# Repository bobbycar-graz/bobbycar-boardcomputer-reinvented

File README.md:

# bobbycar-boardcomputer-reinvented
This is a project to reinvent the current board-computer. It is still based on ESP32, but has some new features in hardware and a completely rewritten software.

## Changes

- Updated PCB
  - 2nd Microcontroller for reading the potentiometers
  - Split entertainment / display / cloud from important things
  - Add on-board USB C flasher for both MCUs
  - Newer ESP32 module (ESP32-S3)
- Rewritten software
  - Written from scratch
  - Updated Librarys
  - Programmed for easier customization
  - Toolchains for generating icons etc.

## Documentation
- [PCB](kicad/README.md)
- [Entertainment Firmware](entertainment-firmware/README.md)
- [Input Firmware](input-firmware/README.md)

## New Structure

The idea is to split the old board-computer into multiple parts:
1. The entertainment system
2. The input system

The input system will feature a non-ESP MCU (Arduino, STM,... *TBD*) that has some config options to modify the control behavior. It will make some calculations based on config and send the result via CAN to the motor-controllers.

The entertainment system will only receive CAN-Messages, which will then be displayed or relayed to the cloud. It will also have a USB-C port for flashing the firmware. The entertainment system will be based on ESP32-S3. We will continue to use the display from the old board-computer (ILI9341 320x240).

Before implementing UI, there should be some kind of sketch to see how it will look like.

## Development Flow

To ensure quality, there will be a development flow. Before ordering PCBs, we will have meetings to see what we can improve. When we build the software, we talk and communicate in a way that each team member understands what the plan is.

If there is some bug or a new feature, **always** document it using issues. Only then start to work on it.

Feel free to make a Pull Request!

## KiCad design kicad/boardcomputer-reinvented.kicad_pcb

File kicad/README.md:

# bobbycar-boardcomputer-reinvented PCB / KiCAD
This PCB will have both MCUs, a few connectors and a USB-C port for flashing.

## Ideas
- USB-C for flashing
  - For reducing costs, only have one USB-C port on the PCB and use some kind of switch (for example DIP switches) to select which MCU to flash. (TBD if this can work) -> No, 

## Requirements
- 2x Display Header (just two different EN pins)
- 1x buzzer
- 12V Input seperated from CAN 12V
- Poti 10k
- Connect MCUs with UART

## Resources
- ESP32 S3:  https://www.espressif.com/sites/default/files/documentation/esp32-s3_datasheet_en.pdf

## Notes
- [x] Check inter processor UART pins
- [x] Check SPI-Display pins
- [x] Check CAN pins
- [x] Beeper connected to +3V3 instead of +5V
- [x] ~Check J5 lcsc and footprint~
- [x] Check Strapping Pins & SPI Flash Voltage (Section Below Strapping Pins) (https://www.espressif.com/sites/default/files/documentation/esp32-s3_datasheet_en.pdf#cd-pins-strap)

## PDFs
There are exported PDFs in the `export` folder. These can be updated using the shell script `scripts/generate_pdfs.sh`.

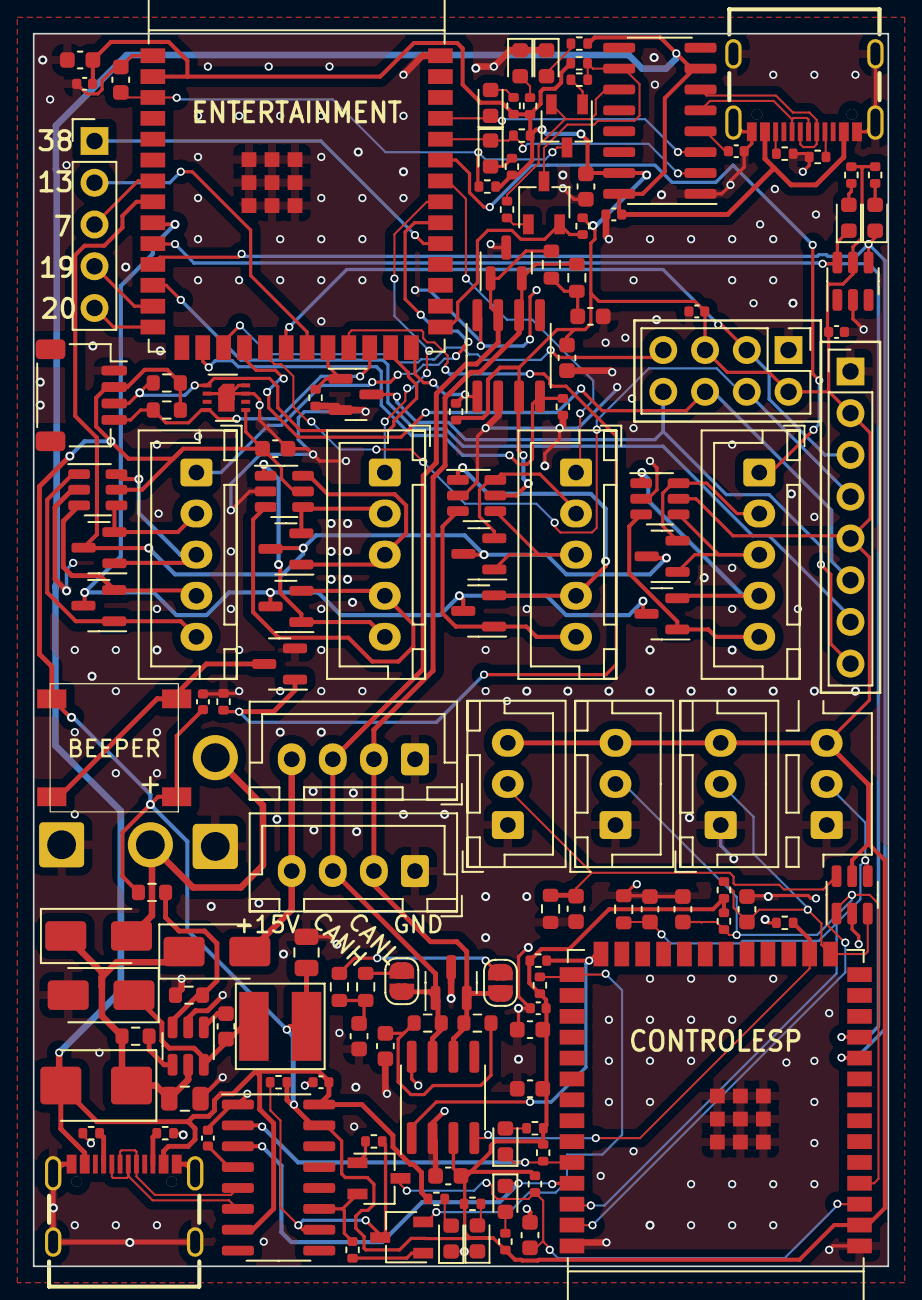
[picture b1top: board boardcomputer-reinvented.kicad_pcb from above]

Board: 2 copper layers, 52.0 x 75.0 mm, 141 parts (0 on the bottom side), 101 nets.

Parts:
BZ1: Buzzer
C1, C3, C6, C7, C9, C12, C20, C21, C28: 100n; C_0402_1005Metric
C2, C8: 1u; C_0603_1608Metric
C4, C5, C10, C11: 10u; C_0603_1608Metric
C13, C15: 22uF; C_0805_2012Metric
C14: 10n; C_0603_1608Metric
C16, C17, C18, C19, C24, C25, C26, C27: 100n; C_0603_1608Metric
C23, C29: 100nF; C_0603_1608Metric
D1, D2, D3, D5, D6, D7, D23, D24: LED; LED_0603_1608Metric
D4, D8: LED5V; LED_0603_1608Metric
D9, D11, D14: B230A; D_SMA
D10: D; D_SMB
D12, D13: NUP2105L; SOT-23
D15, D16, D17, D18, D19, D20, D21, D22: BAV99; SOT-23
J1: CAN1; JST_XH_B4B-XH-A_1x04_P2.50mm_Vertical
J2: CAN2; JST_XH_B4B-XH-A_1x04_P2.50mm_Vertical
J3: Conn_Display; PinHeader_1x08_P2.54mm_Vertical
J4: Conn_Display; PinHeader_2x04_P2.54mm_Vertical
J5, J13: Conn_01x02_Pin; SolderWire-1sqmm_1x02_P5.4mm_D1.4mm_OD2.7mm
J6: BUTTON2; JST_XH_B5B-XH-A_1x05_P2.50mm_Vertical
J7: BUTTON3; JST_XH_B5B-XH-A_1x05_P2.50mm_Vertical
J8, J9: GAS; JST_XH_B3B-XH-A_1x03_P2.50mm_Vertical
J10, J11: BREMSE; JST_XH_B3B-XH-A_1x03_P2.50mm_Vertical
J12: I2C; JST_SH_SM04B-SRSS-TB_1x04-1MP_P1.00mm_Horizontal
J14: Conn_01x05_Pin; PinHeader_1x05_P2.54mm_Vertical
J16: BUTTON1; JST_XH_B5B-XH-A_1x05_P2.50mm_Vertical
J17: BUTTON4; JST_XH_B5B-XH-A_1x05_P2.50mm_Vertical
JP3, JP4: SolderJumper_2_Open; SolderJumper-2_P1.3mm_Open_RoundedPad1.0x1.5mm
L1: 4.7uH; L_5040
Q1, Q2, Q3, Q4: SS8050_C2150; TSOT-23
Q5, Q6: 2N7002; SOT-23
R1, R2, R12, R13: 12k; R_0402_1005Metric
R3, R4, R14, R15: 5k1; R_0402_1005Metric
R5, R6, R16, R17, R32, R33, R34, R35, R36, R37, R38, R39: 10k; R_0402_1005Metric
R7, R8, R9, R10, R11, R18, R19, R20, R21, R22, R23, R24, R46, R47: 1k; R_0402_1005Metric
R25: 1k; R_0603_1608Metric
R26: 49.9k; R_0603_1608Metric
R27: 16.2k; R_0603_1608Metric
R28, R29, R30, R31: 56R; R_0603_1608Metric
R40, R41: 2k2; R_0603_1608Metric
R42, R43: 100k; R_0603_1608Metric
R48, R49: 56; R_0603_1608Metric
U1, U3: CH343G; SOIC-16_3.9x9.9mm_P1.27mm
U2: ESP32-S3-WROOM-1-ENTERTAINMENT; ESP32-S3-WROOM-1
U4: ESP32-S3-WROOM-1-CONTROL; ESP32-S3-WROOM-1
U5: MPM2359; SOT-23-6
U6, U7: SN65HVD231; SOIC-8_3.9x4.9mm_P1.27mm
U8, U9, U10, U11, U13, U14: USBLC6-4SC6; SOT-23-6
U12: SHT30-DIS; Sensirion_DFN-8-1EP_2.5x2.5mm_P0.5mm_EP1.1x1.7mm
USBC1, USBC2: MC-311D; USB-C-SMD_MC-311D

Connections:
15V: C13.2, D10.1 (K), D11.1 (K), D14.1 (K), R25.2, U5.5 (IN)
+3.3V: BZ1.1 (-), C2.2, C5.2, C6.2, C8.2, C11.2, C12.2, C15.2, C16.1, C18.1, C20.1, C21.1, C23.1, C28.1, J3.2, J3.5, J4.2, J4.5, J8.3, J9.3, J10.3, J11.3, J12.2, L1.2, R5.2, R6.2, R7.1, R8.1, R9.1, R11.1, R16.2, R17.2, R18.1, R19.1, R20.1, R22.1, R23.1, R24.1, R26.2, R36.1, R37.2, R38.1, R39.2, R40.2, R41.2, R46.1, R47.1, U1.15 (VIO), U2.2 (3V3), U3.15 (VIO), U4.2 (3V3), U6.3 (VCC), U7.3 (VCC), U8.5 (VBUS), U9.5 (VBUS), U10.5 (VBUS), U11.5 (VBUS), U12.5 (VDD), U13.5 (VBUS), U14.5 (VBUS)
+5V: C1.2, C7.2, D10.2 (A), R10.1, R21.1, U1.7 (VBUS), U1.16 (VDD5), U3.7 (VBUS), U3.16 (VDD5), USBC1.A4-B9 (VBUS), USBC1.B4-A9 (VBUS), USBC2.A4-B9 (VBUS), USBC2.B4-A9 (VBUS)
/CONTROLESP_EN: C10.2, Q3.3 (C), R24.2, U4.3 (EN)
/CONTROLESP_IO0: Q4.2 (E), R22.2, U4.27 (GPIO0/BOOT)
/CONTROLESP_RX: D5.1 (K), R16.1, U3.2 (TXD), U4.36 (U0RXD/GPIO44/CLK_OUT2)
/CONTROLESP_TX: D6.1 (K), U3.3 (RXD), U4.37 (U0TXD/GPIO43/CLK_OUT1)
/ENTERTAINMENT_EN: C4.2, Q1.3 (C), R23.2, U2.3 (EN)
/ENTERTAINMENT_IO0: Q2.2 (E), R11.2, U2.27 (GPIO0/BOOT)
/ENTERTAINMENT_RX: D1.1 (K), R5.1, U1.2 (TXD), U2.36 (U0RXD/GPIO44/CLK_OUT2)
/ENTERTAINMENT_TX: D2.1 (K), U1.3 (RXD), U2.37 (U0TXD/GPIO43/CLK_OUT1)
/Flasher1/DTR: Q4.3 (C), R12.1, R17.1, U3.10 (~DTR/TNOW)
/Flasher1/RTS: Q3.2 (E), R13.1, U3.11 (~RTS)
/Flasher1/USB_DN: U3.6 (UD-), USBC2.A7 (DN1), USBC2.B7 (DN2)
/Flasher1/USB_DP: U3.5 (UD+), USBC2.A6 (DP1), USBC2.B6 (DP2)
/Flasher/DTR: Q2.3 (C), R1.1, R6.1, U1.10 (~DTR/TNOW)
/Flasher/RTS: Q1.2 (E), R2.1, U1.11 (~RTS)
/Flasher/USB_DN: U1.6 (UD-), USBC1.A7 (DN1), USBC1.B7 (DN2)
/Flasher/USB_DP: U1.5 (UD+), USBC1.A6 (DP1), USBC1.B6 (DP2)
B1: D15.1 (K), J16.5, U9.1 (I/O1)
B2: D15.2 (A), J16.4, U9.3 (I/O2)
B3: D17.1 (K), J7.5, U8.3 (I/O2)
B4: D17.2 (A), J7.4, U8.1 (I/O1)
B5: D19.1 (K), J6.5, U11.1 (I/O1)
B6: D19.2 (A), J6.4, U11.3 (I/O2)
B7: D21.1 (K), J17.5, U10.3 (I/O2)
B8: D21.2 (A), J17.4, U10.1 (I/O1)
B9: D16.1 (K), J16.3, U9.6 (I/O4)
B10: D16.2 (A), J16.2, U9.4 (I/O3)
B11: D18.1 (K), J7.3, U8.4 (I/O3)
B12: D18.2 (A), J7.2, U8.6 (I/O4)
B13: D20.1 (K), J6.3, U11.6 (I/O4)
B14: D20.2 (A), J6.2, U11.4 (I/O3)
B15: D22.1 (K), J17.3, U10.4 (I/O3)
B16: D22.2 (A), J17.2, U10.6 (I/O4)
BEEPER: Q5.1 (G), R32.1, U2.23 (GPIO21)
CANH: D12.1 (K), D13.1 (K), J1.3, J2.3, JP3.1 (A), R28.1, R30.1, U6.7 (CANH), U7.7 (CANH)
CANL: D12.2 (K), D13.2 (K), J1.2, J2.2, JP4.2 (B), R29.2, R31.2, U6.6 (CANL), U7.6 (CANL)
CAN_VCC: D11.2 (A), J1.4, J2.4
CONTROLESP_CAN_RX: R35.2, U4.16 (GPIO46), U7.4 (R)
CONTROLESP_CAN_TX: R39.1, U4.26 (GPIO45), U7.1 (D)
DISPLAY_BACKLIGHT: Q6.1 (G), R33.1, U2.22 (GPIO14/TOUCH14/ADC2_CH3/FSPIWP/FSPIDQS/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)
DISPLAY_CS1: J3.7, U2.12 (GPIO8/TOUCH8/ADC1_CH7/SUBSPICS1)
DISPLAY_CS2: J4.7, U2.17 (GPIO9/TOUCH9/ADC1_CH8/FSPIHD/SUBSPIHD)
DISPLAY_DC: J3.6, J4.6, U2.18 (GPIO10/TOUCH10/ADC1_CH9/FSPICS0/FSPIIO4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)
DISPLAY_MOSI: J3.4, J4.4, U2.19 (GPIO11/TOUCH11/ADC2_CH0/FSPID/FSPIIO5/S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)
DISPLAY_SCLK: J3.3, J4.3, U2.20 (GPIO12/TOUCH12/ADC2_CH1/FSPICLK/FSPIIO6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)
ENTERTAINMENT_CAN_RX: R34.2, U2.16 (GPIO46), U6.4 (R)
ENTERTAINMENT_CAN_TX: R37.1, U2.26 (GPIO45), U6.1 (D)
ENTERTAINMENT_GPIO7: J14.3, U2.7 (GPIO7/TOUCH7/ADC1_CH6)
ENTERTAINMENT_GPIO13: J14.2, U2.21 (GPIO13/TOUCH13/ADC2_CH2/FSPIQ/FSPIIO7/S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)
ENTERTAINMENT_GPIO19: J14.4, U2.13 (GPIO19/U1RTS/ADC2_CH8/CLK_OUT2/USB_D-)
ENTERTAINMENT_GPIO20: J14.5, U2.14 (GPIO20/U1CTS/ADC2_CH9/CLK_OUT1/USB_D+)
ENTERTAINMENT_GPIO38: J14.1, U2.31 (GPIO38/FSPIWP/SUBSPIWP)
GND: C1.1, C2.1, C3.1, C4.1, C5.1, C6.1, C7.1, C8.1, C9.1, C10.1, C11.1, C12.1, C13.1, C15.1, C16.2, C17.2, C18.2, C19.2, C20.2, C21.2, C23.2, C24.2, C25.1, C26.1, C27.2, C28.2, C29.2, D3.1 (K), D4.1 (K), D7.1 (K), D8.1 (K), D9.2 (A), D12.3 (A), D13.3 (A), J1.1, J2.1, J3.1, J4.1, J5.1, J8.1, J9.1, J10.1, J11.1, J12.1, J13.1, Q5.2 (S), Q6.2 (S), R3.2, R4.1, R14.2, R15.1, R27.1, R32.2, R33.2, R34.1, R35.1, R42.1, R43.1, U1.1 (GND), U2.1 (GND), U2.40 (GND), U2.41 (GND), U3.1 (GND), U4.1 (GND), U4.40 (GND), U4.41 (GND), U5.2 (GND), U6.2 (GND), U6.8 (Rs), U7.2 (GND), U7.8 (Rs), U8.2 (GND), U9.2 (GND), U10.2 (GND), U11.2 (GND), U12.2 (ADDR), U12.7 (R), U12.8 (VSS), U12.9 (VSS), U13.2 (GND), U14.2 (GND), USBC1.1 (SHIELD), USBC1.2 (SHIELD), USBC1.3 (SHIELD), USBC1.4 (SHIELD), USBC1.A1-B12 (GND), USBC1.B1-A12 (GND), USBC2.1 (SHIELD), USBC2.2 (SHIELD), USBC2.3 (SHIELD), USBC2.4 (SHIELD), USBC2.A1-B12 (GND), USBC2.B1-A12 (GND)
IN1: J16.1, U2.32 (MTCK/GPIO39/CLK_OUT3/SUBSPICS1)
IN2: J6.1, U2.33 (MTDO/GPIO40/CLK_OUT2)
IN3: J7.1, U2.34 (MTDI/GPIO41/CLK_OUT1)
IN4: J17.1, U2.35 (MTMS/GPIO42)
unnamed: BZ1.2 (+), Q5.3 (D)
unnamed: C17.1, R28.2, R29.1
unnamed: C19.1, R30.2, R31.1
unnamed: C29.1, R48.2, R49.1
unnamed: D1.2 (A), R7.2
unnamed: D2.2 (A), R8.2
unnamed: D3.2 (A), R9.2
unnamed: D4.2 (A), R10.2
unnamed: D5.2 (A), R18.2
unnamed: D6.2 (A), R19.2
unnamed: D7.2 (A), R20.2
unnamed: D8.2 (A), R21.2
unnamed: C14.1, D9.1 (K), L1.1, U5.6 (SW)
unnamed: D14.2 (A), J5.2, J13.2
unnamed: D23.2 (A), R46.2
unnamed: D24.2 (A), R47.2
unnamed: J3.8, J4.8, Q6.3 (D)
unnamed: JP3.2 (B), R48.1
unnamed: JP4.1 (A), R49.2
unnamed: Q1.1 (B), R1.2
unnamed: Q2.1 (B), R2.2
unnamed: Q3.1 (B), R12.2
unnamed: Q4.1 (B), R13.2
unnamed: C3.2, U1.4 (V3)
unnamed: C9.2, U3.4 (V3)
unnamed: C14.2, U5.1 (BST)
unnamed: R25.1, U5.4 (EN)
unnamed: R26.1, R27.2, U5.3 (FB)
unnamed: R3.1, USBC1.A5 (CC1)
unnamed: R4.2, USBC1.B5 (CC2)
unnamed: R14.1, USBC2.A5 (CC1)
unnamed: R15.2, USBC2.B5 (CC2)
OUT1: D15.3 (K), D17.3 (K), D19.3 (K), D21.3 (K), U2.9 (GPIO16/U0CTS/ADC2_CH5/XTAL_32K_N)
OUT2: D16.3 (K), D18.3 (K), D20.3 (K), D22.3 (K), U2.8 (GPIO15/U0RTS/ADC2_CH4/XTAL_32K_P)
PROCESSOR_COMMUNICATION_CONTROLESP_RX: D24.1 (K), U2.10 (GPIO17/U1TXD/ADC2_CH6), U4.11 (GPIO18/U1RXD/ADC2_CH7/CLK_OUT3), U14.6 (I/O4)
PROCESSOR_COMMUNICATION_CONTROLESP_TX: D23.1 (K), U2.11 (GPIO18/U1RXD/ADC2_CH7/CLK_OUT3), U4.10 (GPIO17/U1TXD/ADC2_CH6), U14.4 (I/O3)
RAW_BREMSE: C26.2, J10.2, R36.2, U4.15 (GPIO3/TOUCH3/ADC1_CH2), U13.3 (I/O2)
RAW_GAS: C25.2, J8.2, R38.2, U4.4 (GPIO4/TOUCH4/ADC1_CH3), U13.1 (I/O1)
RAW_M365_BREMSE: C27.1, J11.2, R43.2, U4.39 (GPIO1/TOUCH1/ADC1_CH0), U13.6 (I/O4)
RAW_M365_GAS: C24.1, J9.2, R42.2, U4.38 (GPIO2/TOUCH2/ADC1_CH1), U13.4 (I/O3)
SCL: J12.4, R40.1, U2.24 (GPIO47/SPICLK_P/SUBSPICLK_P_DIFF), U12.4 (SCL)
SDA: J12.3, R41.1, U2.25 (GPIO48/SPICLK_N/SUBSPICLK_N_DIFF), U12.1 (SDA)

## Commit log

2023-05-29 Added links
2023-05-30 Created README.md
2023-05-30 Added whiteboard picture
2023-05-30 Added whiteboard picture to README
2023-05-30 Fix path
2023-07-08 Initial schematic
2023-07-08 Cleanups
2023-07-09 Finished routing
2023-07-09 Export PDFs
2023-07-09 Updated pcb
